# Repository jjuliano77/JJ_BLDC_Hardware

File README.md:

# JJ_BLDC_Hardware
Eagle CAD files for my BLDC motor controller

There are a number of problems with this board design as it is. There are traces missing for the hardware overcurrent protection control on the DRV8302, the footprint for the buck converter inductor is not right, and I want to have the option of just using a single shunt for current sensing. I'm sure there are other problems too.

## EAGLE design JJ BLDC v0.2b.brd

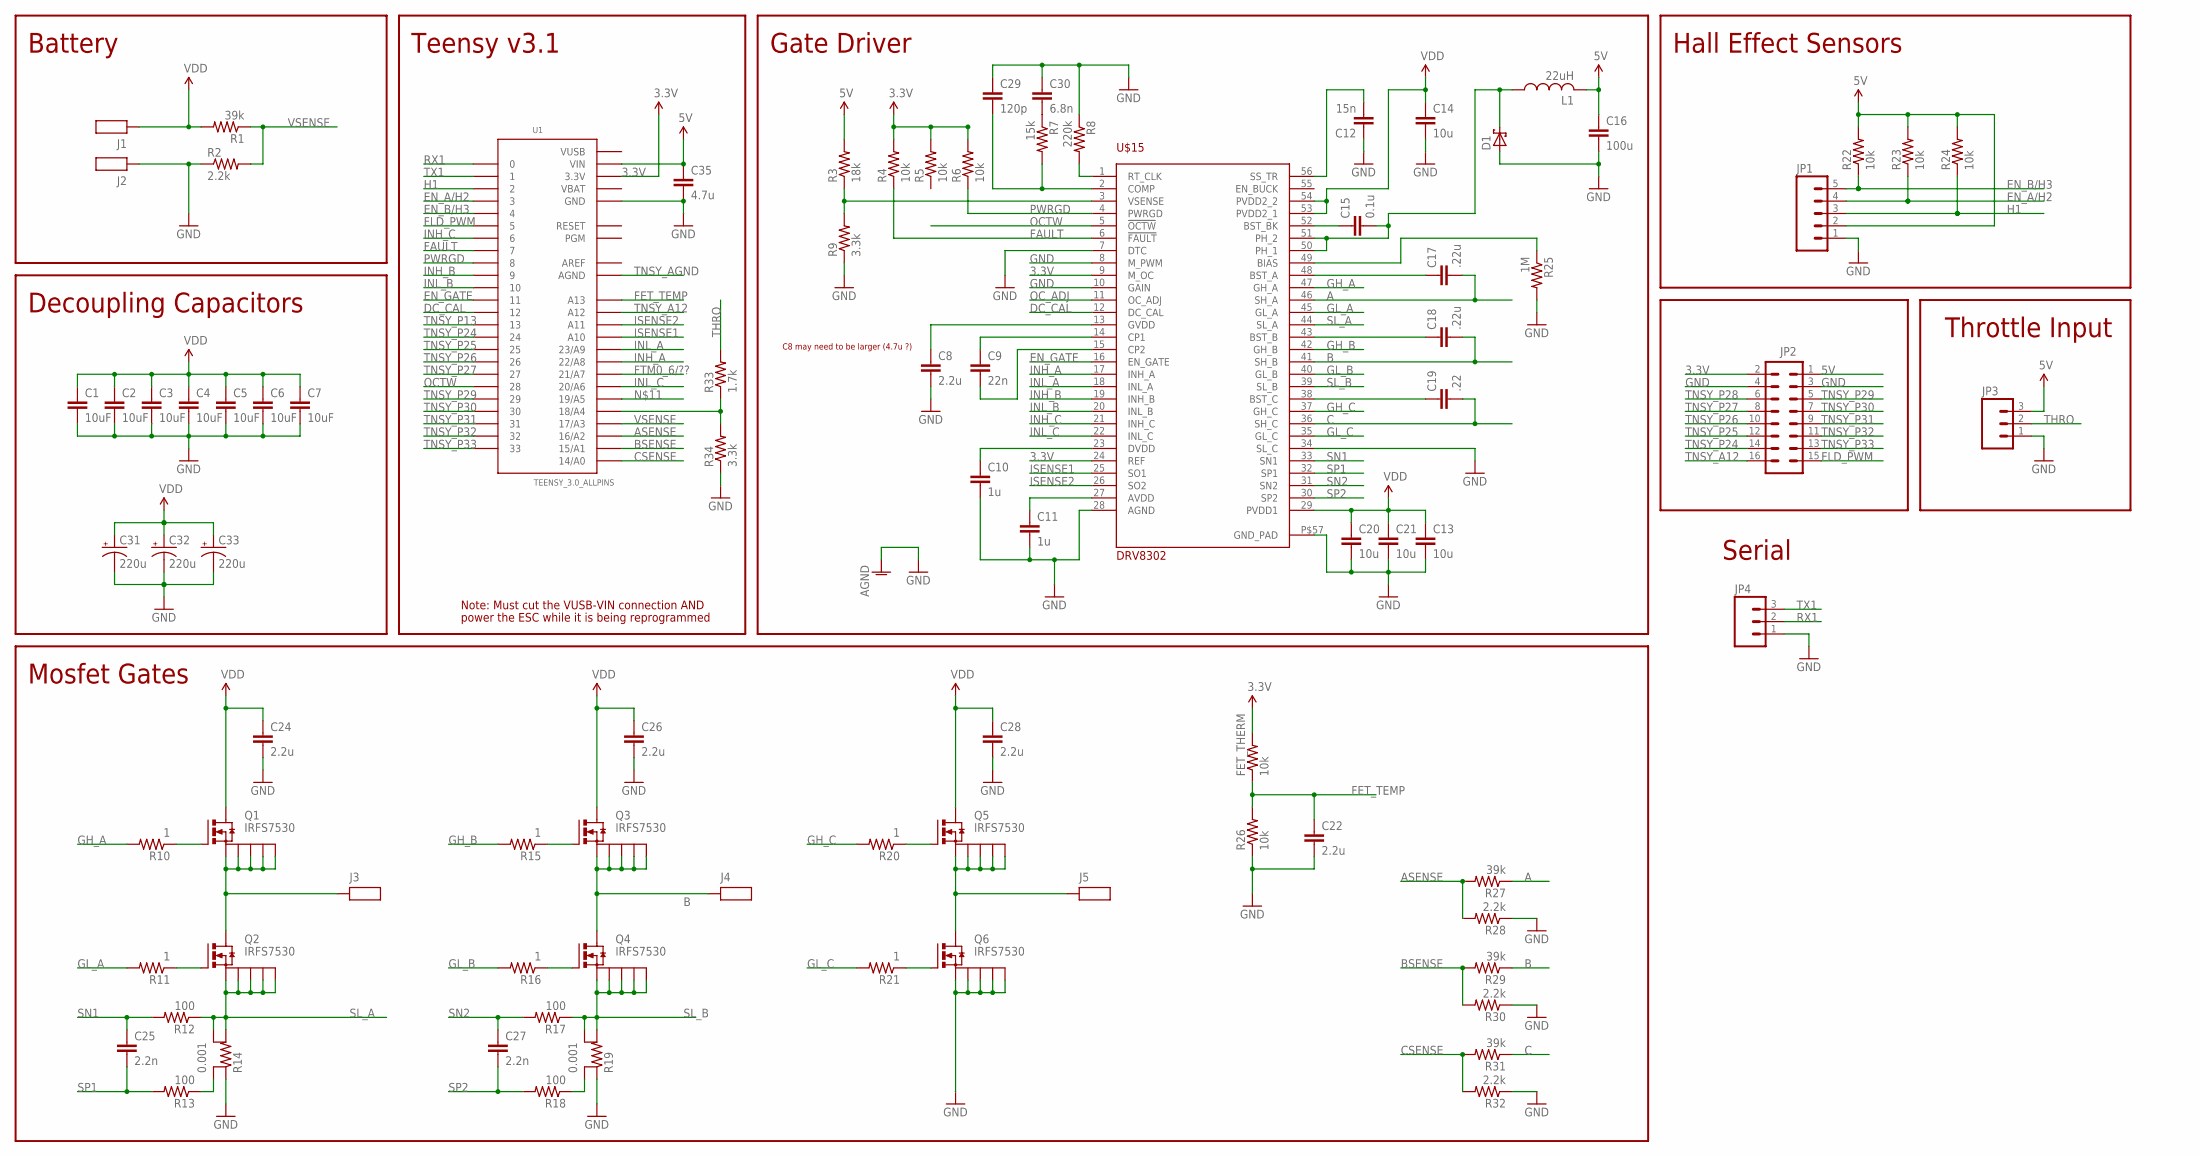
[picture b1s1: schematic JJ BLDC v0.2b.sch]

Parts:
C1, C2, C3, C4, C5, C6, C7: 10uF; 1206
C8, C22: 2.2u; 0603-CAP
C9: 22n; 0603-CAP
C10, C11: 1u; 0603-CAP
C12: 15n; 0603-CAP
C13, C14, C21: 10u; 0805
C15: 0.1u; 0603-CAP
C16: 100u; 0805
C17, C18: .22u; 0603-CAP
C19: .22; 0603-CAP
C20: 10u; 0603-CAP
C24, C26, C28: 2.2u; 1206
C25, C27: 2.2n; 0603-CAP
C29: 120p; 0603-CAP
C30: 6.8n; 0603-CAP
C31, C32, C33: 220u; E5-10,5
C35: 4.7u; 0603-CAP
D1: SCHOTTKY_SMA; SMA
FET_THERM: 10k; 0603-RES
J1, J2, J3, J4, J5: WIREPAD_SMD_10X4
JP1: M05PTH; 1X05
JP2: M08X2; 2X8
JP3, JP4: M03PTH; 1X03
L1: 22uH; L5650M
Q1, Q2, Q3, Q4, Q5, Q6: IRFS7530; TO-263-7
R1, R27, R29, R31: 39k; 0603-RES
R2, R28, R30, R32: 2.2k; 0603-RES
R3: 18k; 0603-RES
R4, R5, R6, R22, R23, R24, R26: 10k; 0603-RES
R7: 15k; 0603-RES
R8: 220k; 0603-RES
R9, R34: 3.3k; 0603-RES
R10, R11, R15, R16, R20, R21: 1; 0603-RES
R12, R13, R17, R18: 100; 0603-RES
R14, R19: 0.001; SHUNT-RES-2726
R25: 1M; 0603-RES
R33: 1.7k; 0603-RES
U1: TEENSY_3.0_ALLPINS
U$15: DRV8302; HTSSOP-56

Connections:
3.3V: FET_THERM.2, JP2.2, R4.2, R5.2, R6.2, U1.3.3V, U1.3.3V1 (3.3V), U1.3.3V2 (3.3V), U$15.9 (M_OC), U$15.24 (REF)
5V: C16.1, C35.1, JP1.2, JP2.1, JP3.3, L1.2, R3.2, R22.2, R23.2, R24.2, U1.VIN
A: C17.2, J3.P$1, Q1.2 (S1), Q1.3 (S2), Q1.5 (S3), Q1.6 (S4), Q1.7 (S), Q2.4 (D), R27.1, U$15.46 (SH_A)
AREF: U1.AREF
ASENSE: R27.2, R28.2, U1.16/A2
B: C18.2, J4.P$1, Q3.2 (S1), Q3.3 (S2), Q3.5 (S3), Q3.6 (S4), Q3.7 (S), Q4.4 (D), R29.1, U$15.41 (SH_B)
BSENSE: R29.2, R30.2, U1.15/A1
C: C19.2, J5.P$1, Q5.2 (S1), Q5.3 (S2), Q5.5 (S3), Q5.6 (S4), Q5.7 (S), Q6.4 (D), R31.1, U$15.36 (SH_C)
CSENSE: R31.2, R32.2, U1.14/A0
DC_CAL: U1.12, U$15.12 (DC_CAL)
EN_A/H2: JP1.4, R23.1, U1.3
EN_B/H3: JP1.5, R22.1, U1.4
EN_GATE: U1.11, U$15.16 (EN_GATE)
FAULT: R4.1, U1.7, U$15.6 (!FAULT)
FET_TEMP: C22.1, FET_THERM.1, R26.2, U1.A13
FLD_PWM: JP2.15, U1.5
FTM0_6/??: U1.21/A7
GH_A: R10.2, U$15.47 (GH_A)
GH_B: R15.2, U$15.42 (GH_B)
GH_C: R20.2, U$15.37 (GH_C)
GL_A: R11.2, U$15.45 (GL_A)
GL_A': Q2.1 (G), R11.1
GL_B: R16.2, U$15.40 (GL_B)
GL_B': Q4.1 (G), R16.1
GL_C: R21.2, U$15.35 (GL_C)
GL_C': Q6.1 (G), R21.1
GND: C1.2, C2.2, C3.2, C4.2, C5.2, C6.2, C7.2, C8.2, C10.2, C11.2, C12.1, C13.2, C14.2, C16.2, C20.2, C21.2, C22.2, C24.2, C26.2, C28.2, C29.1, C30.1, C31.-, C32.-, C33.-, C35.2, D1.A, J2.P$1, JP1.1, JP2.3, JP2.4, JP3.1, JP4.1, Q6.2 (S1), Q6.3 (S2), Q6.5 (S3), Q6.6 (S4), Q6.7 (S), R2.1, R8.1, R9.1, R14.P$1 (1), R19.P$1 (1), R25.2, R26.1, R28.1, R30.1, R32.1, R34.1, U1.GND, U1.GND1 (GND), U1.GND2 (GND), U$15.7 (DTC), U$15.8 (M_PWM), U$15.10 (GAIN), U$15.28 (AGND), U$15.34 (SL_C), U$15.P$57 (GND_PAD)
H1: JP1.3, R24.1, U1.2
INH_A: U1.22/A8, U$15.17 (INH_A)
INH_B: U1.9, U$15.19 (INH_B)
INH_C: U1.6, U$15.21 (INH_C)
INL_A: U1.23/A9, U$15.18 (INL_A)
INL_B: U1.10, U$15.20 (INL_B)
INL_C: U1.20/A6, U$15.22 (INL_C)
ISENSE1: U1.A10, U$15.25 (SO1)
ISENSE2: U1.A11, U$15.26 (SO2)
unnamed: Q3.1 (G), R15.1
unnamed: R3.1, R9.2, U$15.3 (VSENSE)
unnamed: C29.2, R7.2, U$15.2 (COMP)
unnamed: C10.1, U$15.23 (DVDD)
unnamed: Q5.1 (G), R20.1
unnamed: C12.2, U$15.56 (SS_TR)
unnamed: C30.2, R7.1
unnamed: C15.1, U$15.52 (BST_BK)
unnamed: Q1.1 (G), R10.1
unnamed: R8.2, U$15.1 (RT_CLK)
unnamed: R25.1, U$15.49 (BIAS)
unnamed: R33.1, R34.2, U1.18/A4
unnamed: R13.1, R14.P$3
unnamed: R18.1, R19.P$3
unnamed: C19.1, U$15.38 (BST_C)
unnamed: C9.1, U$15.14 (CP1)
unnamed: C11.1, U$15.27 (AVDD)
unnamed: C9.2, U$15.15 (CP2)
unnamed: C8.1, U$15.13 (GVDD)
unnamed: C18.1, U$15.43 (BST_B)
unnamed: C17.1, U$15.48 (BST_A)
unnamed: C15.2, D1.C, L1.1, U$15.50 (PH_1), U$15.51 (PH_2)
OCTW: U1.28, U$15.5 (!OCTW)
OC_ADJ: U$15.11 (OC_ADJ)
PWRGD: R6.1, U1.8, U$15.4 (PWRGD)
RX1: JP4.2, U1.0
SL_A: Q2.2 (S1), Q2.3 (S2), Q2.5 (S3), Q2.6 (S4), Q2.7 (S), R12.1, R14.P$2 (2), R14.P$4, U$15.44 (SL_A)
SL_B: Q4.2 (S1), Q4.3 (S2), Q4.5 (S3), Q4.6 (S4), Q4.7 (S), R17.1, R19.P$2 (2), R19.P$4, U$15.39 (SL_B)
SN1: C25.1, R12.2, U$15.33 (SN1)
SN2: C27.1, R17.2, U$15.31 (SN2)
SP1: C25.2, R13.2, U$15.32 (SP1)
SP2: C27.2, R18.2, U$15.30 (SP2)
THRO: JP3.2, R33.2
TNSY_A12: JP2.16, U1.A12
TNSY_AGND: U1.AGND
TNSY_P13: U1.13
TNSY_P24: JP2.14, U1.24
TNSY_P25: JP2.12, U1.25
TNSY_P26: JP2.10, U1.26
TNSY_P27: JP2.8, U1.27
TNSY_P28: JP2.6
TNSY_P29: JP2.5, U1.29
TNSY_P30: JP2.7, U1.30
TNSY_P31: JP2.9, U1.31
TNSY_P32: JP2.11, U1.32
TNSY_P33: JP2.13, U1.33
TX1: JP4.3, U1.1
VBAT: U1.VBAT
VDD: C1.1, C2.1, C3.1, C4.1, C5.1, C6.1, C7.1, C13.1, C14.1, C20.1, C21.1, C24.1, C26.1, C28.1, C31.+, C32.+, C33.+, J1.P$1, Q1.4 (D), Q3.4 (D), Q5.4 (D), R1.2, U$15.29 (PVDD1), U$15.53 (PVDD2_1), U$15.54 (PVDD2_2)
VSENSE: R1.1, R2.2, U1.17/A3
VUSB: U1.VUSB

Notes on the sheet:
Teensy v3.1
Gate Driver
Mosfet Gates
Battery
Hall Effect Sensors
Decoupling Capacitors
Note: Must cut the VUSB-VIN connection AND
power the ESC while it is being reprogrammed
Throttle Input
C8 may need to be larger (4.7u ?)
Serial

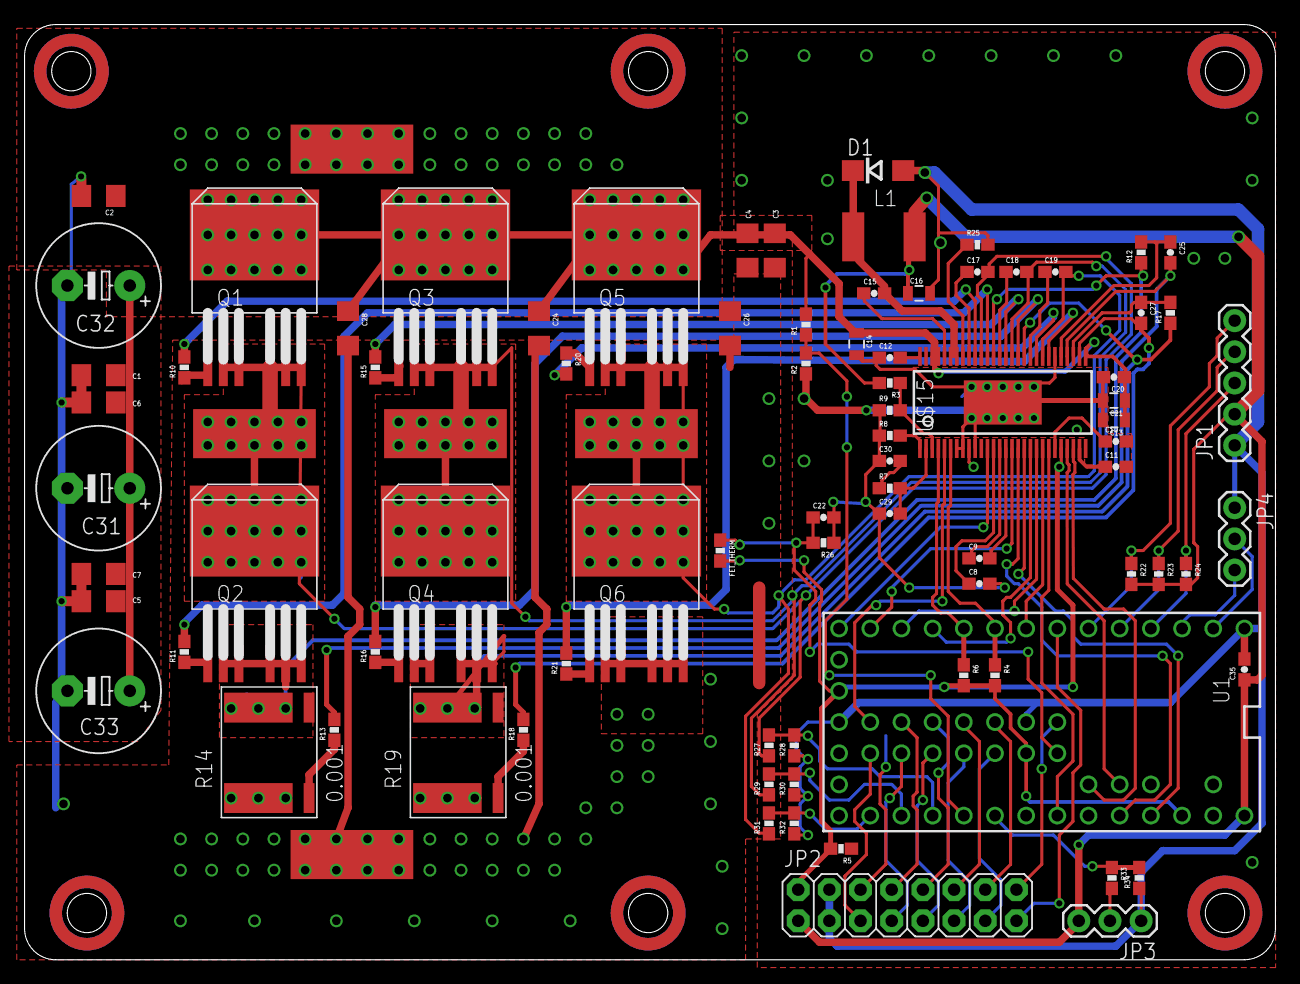
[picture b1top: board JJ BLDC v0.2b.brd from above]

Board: 2 copper layers, 101.9 x 76.2 mm, 87 parts (0 on the bottom side), 79 nets.

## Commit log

2016-06-19 Update README.md
    Added note that the design doesn't work as is.

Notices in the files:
parts and their libraries:
SparkFun-Capacitors: Licensing: Creative Commons ShareAlike 4.0 International - https://creativecommons.org/licenses/by-sa/4.0
